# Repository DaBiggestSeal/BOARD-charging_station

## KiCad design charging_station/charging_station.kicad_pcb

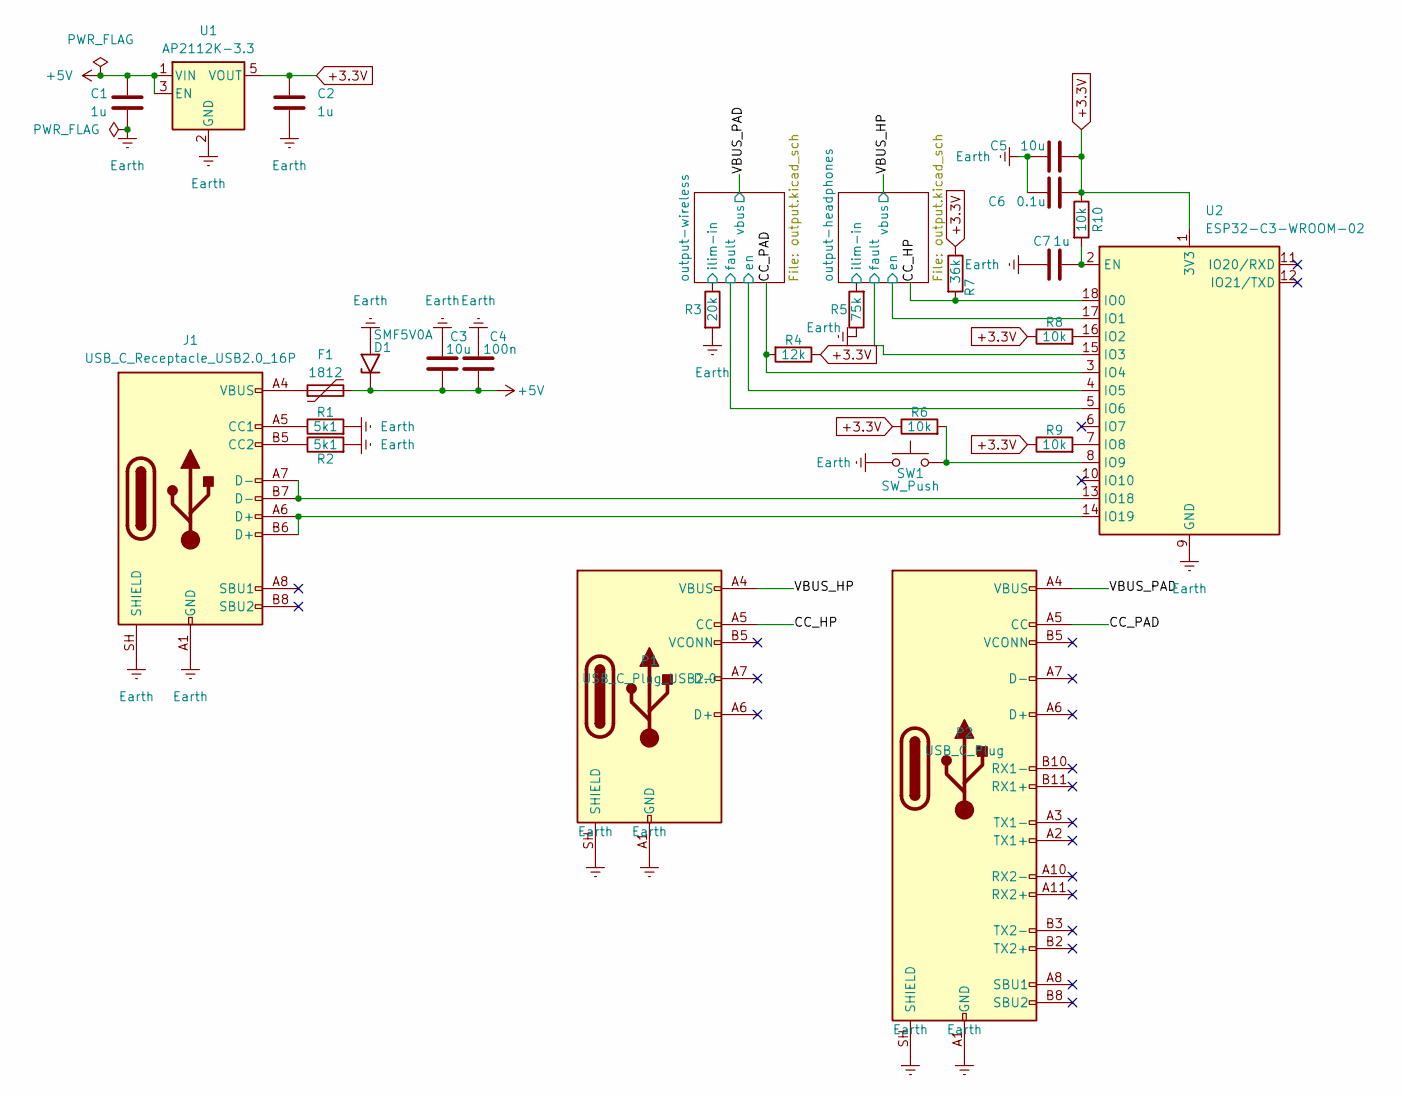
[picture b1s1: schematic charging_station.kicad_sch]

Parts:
C1, C2, C7: 1u; C_0805_2012Metric
C3, C5: 10u; C_0805_2012Metric
C4: 100n; C_0805_2012Metric
C6: 0.1u; C_0805_2012Metric
D1: SMF5V0A; D_SMF
F1: 1812; Fuse_1812_4532Metric
J1: USB_C_Receptacle_USB2.0_16P; USB_C_Receptacle_HRO_TYPE-C-31-M-12
P1: USB_C_Plug_USB2.0; USB_C_Plug_ShenzhenJingTuoJin_918-118A2021Y40002_Vertical
P2: USB_C_Plug; USB_C_Plug_Molex_105444
R1, R2: 5k1; R_0805_2012Metric
R3: 20k; R_0805_2012Metric
R4: 12k; R_0805_2012Metric
R5: 75k; R_0805_2012Metric
R6, R8, R9, R10: 10k; R_0805_2012Metric
R7: 36k; R_0805_2012Metric
SW1: SW_Push; SW_SPST_PTS645Sx43SMTR92
U1: AP2112K-3.3; SOT-23-5
U2: ESP32-C3-WROOM-02

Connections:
+3.3V: C2.1, C5.2, C6.2, R4.1, R6.1, R7.1, R8.1, R9.1, R10.1, U1.5 (VOUT), U2.1 (3V3); also elsewhere on the board
+5V: C1.2, C3.2, C4.1, D1.1 (A1), F1.2, U1.1 (VIN), U1.3 (EN); also elsewhere on the board
/CC_HP: P1.A5 (CC), R7.2, U2.18 (IO0)
/CC_PAD: P2.A5 (CC), R4.2, U2.3 (IO4)
/VBUS_HP: P1.A4 (VBUS), P1.A9 (VBUS), P1.B4 (VBUS), P1.B9 (VBUS); also elsewhere on the board
/VBUS_PAD: P2.A4 (VBUS), P2.A9 (VBUS), P2.B4 (VBUS), P2.B9 (VBUS); also elsewhere on the board
/output-headphones/en: U2.17 (IO1); also elsewhere on the board
/output-headphones/fault: U2.15 (IO3); also elsewhere on the board
/output-headphones/ilim-in: R5.2; also elsewhere on the board
/output-wireless/en: U2.4 (IO5); also elsewhere on the board
/output-wireless/fault: U2.5 (IO6); also elsewhere on the board
/output-wireless/ilim-in: R3.1; also elsewhere on the board
Earth: C1.1, C2.2, C3.1, C4.2, C5.1, C6.1, C7.2, D1.2 (A2), J1.A1 (GND), J1.A12 (GND), J1.B1 (GND), J1.B12 (GND), J1.SH (SHIELD), P1.A1 (GND), P1.A12 (GND), P1.B1 (GND), P1.B12 (GND), P1.SH (SHIELD), P2.A1 (GND), P2.A12 (GND), P2.B1 (GND), P2.B12 (GND), P2.SH (SHIELD), R1.2, R2.2, R3.2, R5.1, SW1.1, U1.2 (GND), U2.9 (GND), U2.19 (GND); also elsewhere on the board
unnamed: F1.1, J1.A4 (VBUS), J1.A9 (VBUS), J1.B4 (VBUS), J1.B9 (VBUS)
unnamed: J1.A5 (CC1), R1.1
unnamed: J1.B5 (CC2), R2.1
unnamed: C7.1, R10.2, U2.2 (EN)
unnamed: R8.2, U2.16 (IO2)
unnamed: R9.2, U2.7 (IO8)
unnamed: R6.2, SW1.2, U2.8 (IO9)
unnamed: J1.A7 (D-), J1.B7 (D-), U2.13 (IO18)
unnamed: J1.A6 (D+), J1.B6 (D+), U2.14 (IO19)

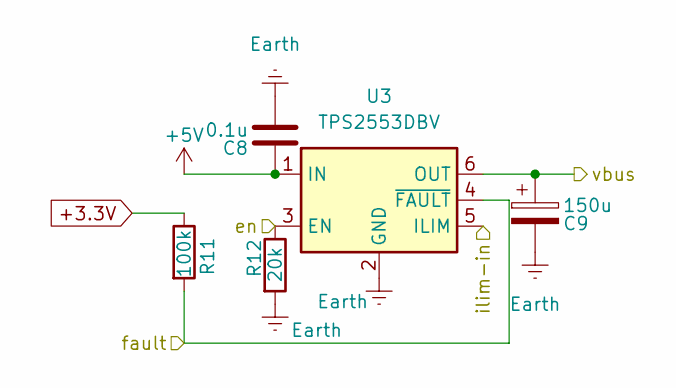
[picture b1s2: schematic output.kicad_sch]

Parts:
C8: 0.1u; C_0805_2012Metric
C9: 150u; CP_EIA-7343-31_Kemet-D
R11: 100k; R_0805_2012Metric
R12: 20k; R_0805_2012Metric
U3: TPS2553DBV; SOT-23-6

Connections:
+3.3V: R11.1; also elsewhere on the board
+5V: C8.2, U3.1 (IN); also elsewhere on the board
/VBUS_HP: C9.1, U3.6 (OUT); also elsewhere on the board
/output-headphones/en: R12.1, U3.3 (EN); also elsewhere on the board
/output-headphones/fault: R11.2, U3.4 (~FAULT); also elsewhere on the board
/output-headphones/ilim-in: U3.5 (ILIM); also elsewhere on the board
Earth: C8.1, C9.2, R12.2, U3.2 (GND); also elsewhere on the board

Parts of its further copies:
C10: 0.1u; C_0805_2012Metric
C11: 150u; CP_EIA-7343-31_Kemet-D
R13: 100k; R_0805_2012Metric
R14: 20k; R_0805_2012Metric
U4: TPS2553DBV; SOT-23-6

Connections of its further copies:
+3.3V: R13.1; also elsewhere on the board
+5V: C10.2, U4.1 (IN); also elsewhere on the board
/VBUS_PAD: C11.1, U4.6 (OUT); also elsewhere on the board
/output-wireless/en: R14.1, U4.3 (EN); also elsewhere on the board
/output-wireless/fault: R13.2, U4.4 (~FAULT); also elsewhere on the board
/output-wireless/ilim-in: U4.5 (ILIM); also elsewhere on the board
Earth: C10.1, C11.2, R14.2, U4.2 (GND); also elsewhere on the board

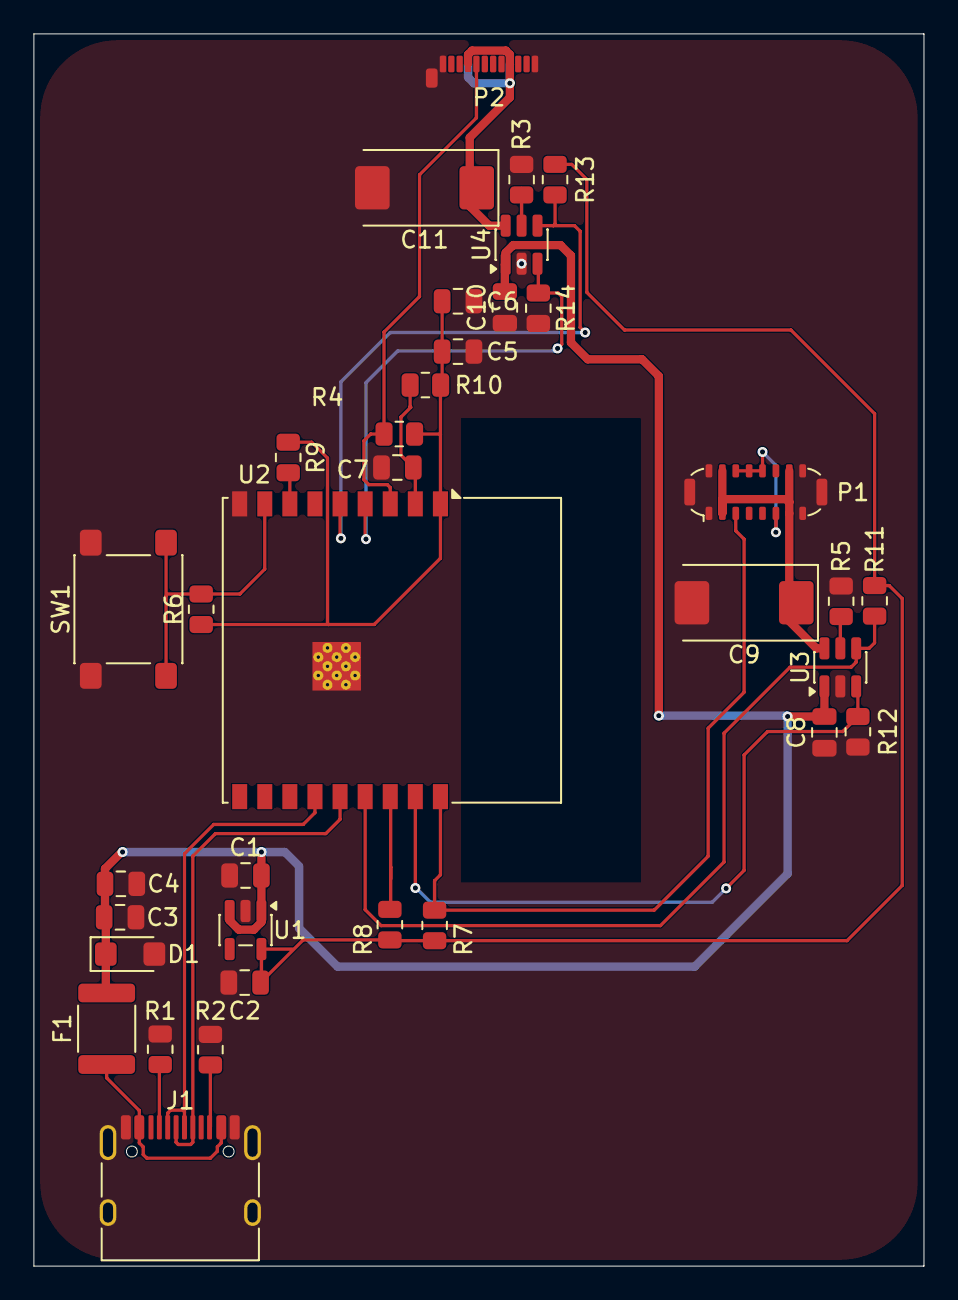
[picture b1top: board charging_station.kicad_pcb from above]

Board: 2 copper layers, 53.2 x 73.6 mm, 35 parts (0 on the bottom side), 22 nets.
